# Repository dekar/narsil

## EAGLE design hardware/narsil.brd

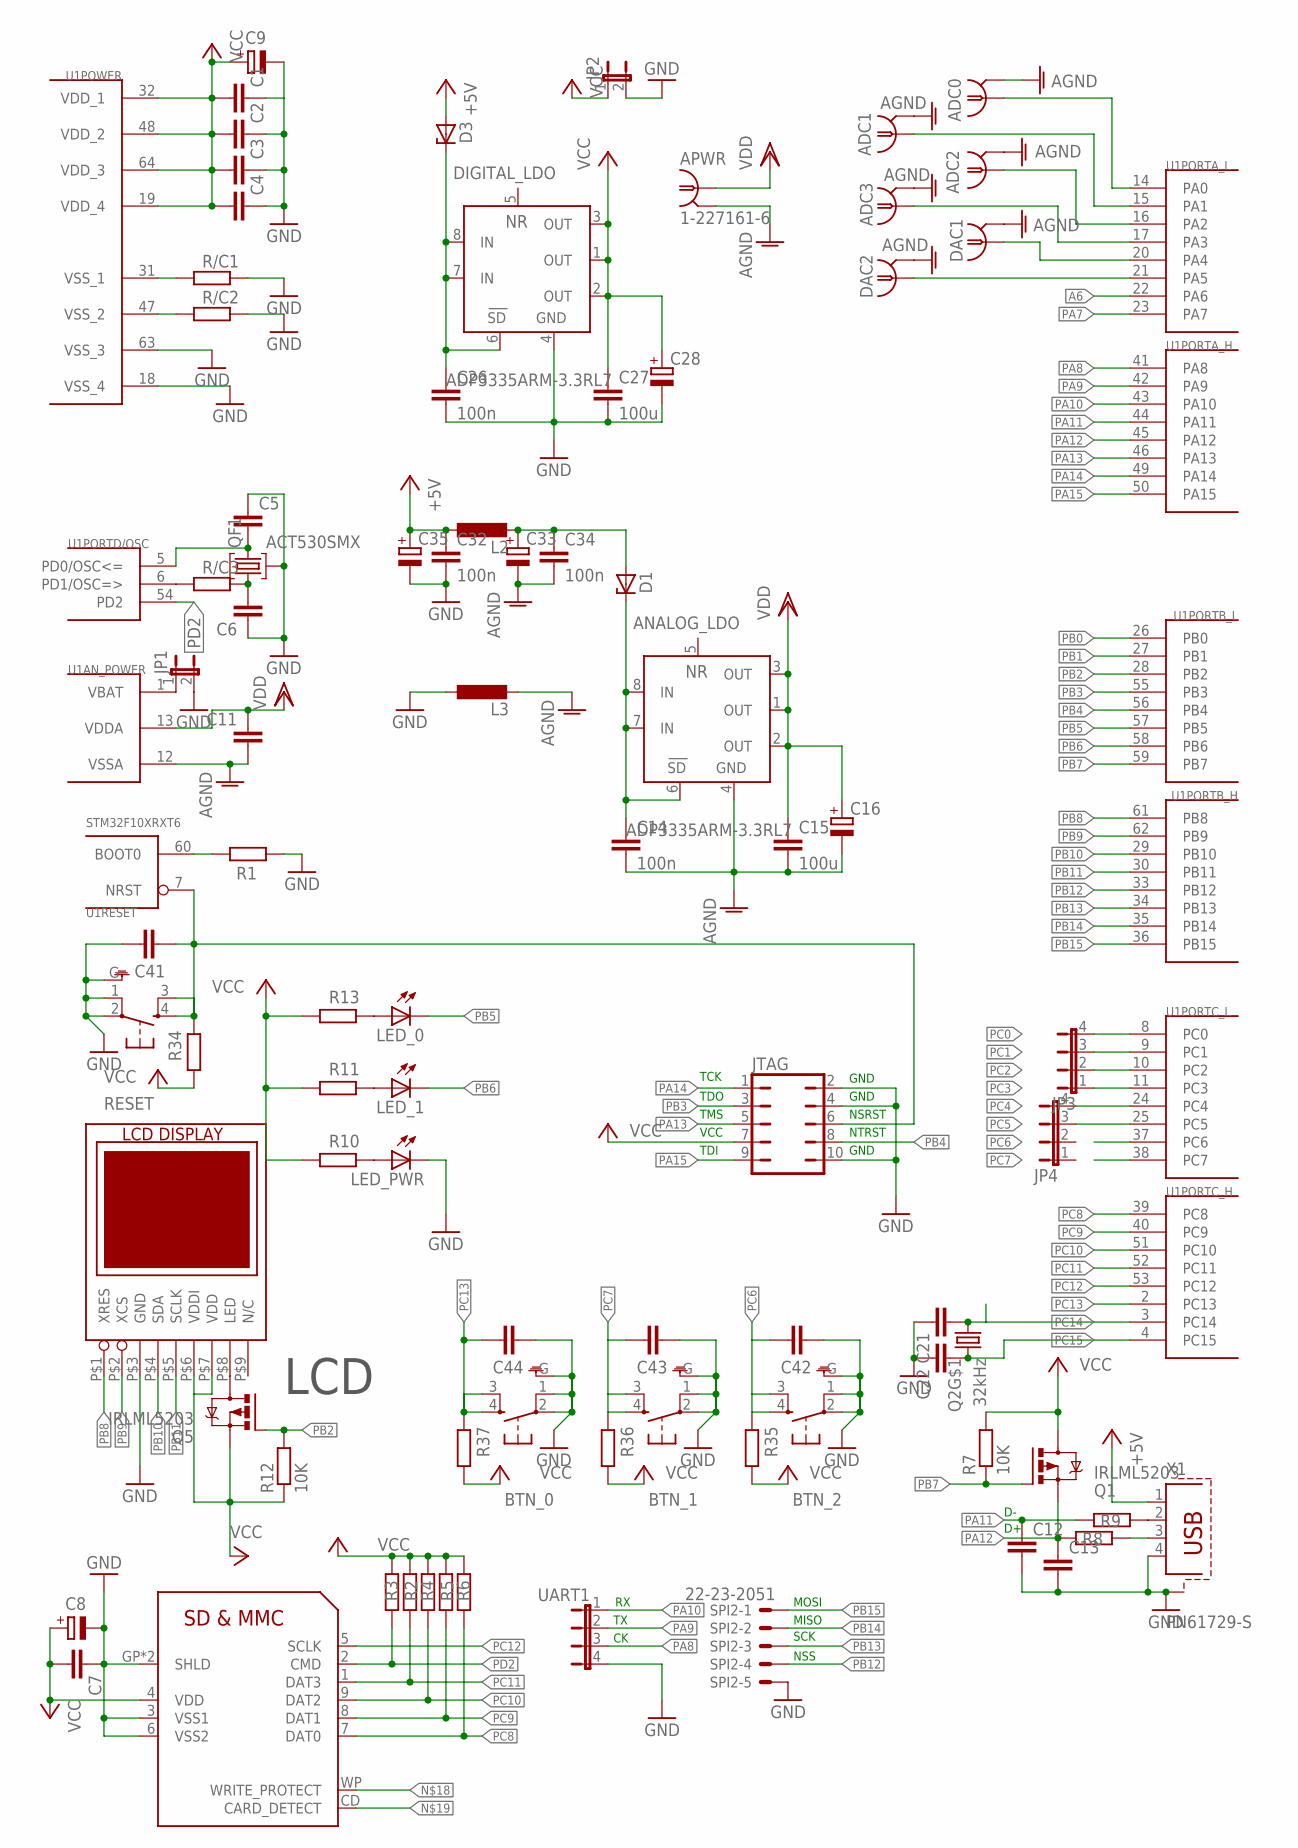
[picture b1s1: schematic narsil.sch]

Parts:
ADC0, ADC1, ADC2: 1-227161-6; AMP_227161
ADC3: 1-227161-6; AMP_227161; MPN 1-227161-6
ANALOG_LDO: ADP3335ARM-3.3RL7; MSOP08
APWR: 1-227161-6; AMP_227161
BTN_0, BTN_1, BTN_2: 10-XXG; B3F-10XXG
C1, C2, C3, C4, C5, C6, C7, C11, C12, C13, C21, C22, C41, C42, C43, C44: C-EUC0805; C0805
C8, C9, C16, C28, C33, C35: CPOL-EUSMCA; SMC_A
C14, C26, C32, C34: 100n; C0805
C15, C27: 100u; C0805
D1, D3: ZENER-DIODESMB; SMB
DAC1, DAC2: 1-227161-6; AMP_227161
DIGITAL_LDO: ADP3335ARM-3.3RL7; MSOP08
JP1, JP2: JP1E; JP1
JP3, JP4: JP4E; JP4
JTAG: JP5Q
L2, L3: L-EUL1206; R1206
LED_0, LED_1: LEDSMT1206; 1206
LED_PWR: LEDSMT1206; 1206
Q1, Q5: IRLML5203; MICRO3
Q2: 32kHz; MC146
QF1: ACT530SMX
R1, R10, R11, R13, R34, R35, R36, R37: 5k; M0805
R2, R3, R4, R5, R6, R8, R9: 47k; M0805
R7, R12: 10K; M0805
R/C1, R/C2, R/C3: R-EU_M0805; M0805
RESET: 10-XXG; B3F-10XXG
SPI2: 22-23-2051
U1: STM32F10XRXT6; TQFP64
U$1: SD-RSMT-2-MQ
U$2: LCD; LCD_NOKIA1100
UART1: JP4E; JP4
X1: PN61729-S

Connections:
+5V: C32.1, C35.+, D3.A, L2.1, X1.1
A6: U1.22 (PA6)
AGND: ADC0.2 (GND), ADC1.2 (GND), ADC2.2 (GND), ADC3.2 (GND), ANALOG_LDO.4 (GND), APWR.2 (GND), C11.2, C14.2, C15.2, C16.-, C33.-, C34.2, DAC1.2 (GND), DAC2.2 (GND), L3.2, U1.12 (VSSA)
GND: BTN_0.1, BTN_0.2, BTN_0.G (GND), BTN_1.1, BTN_1.2, BTN_1.G (GND), BTN_2.1, BTN_2.2, BTN_2.G (GND), C1.1, C2.1, C3.1, C4.1, C5.1, C6.1, C7.1, C8.-, C9.-, C12.2, C13.2, C21.1, C22.1, C26.2, C27.2, C28.-, C32.2, C35.-, C41.1, C42.1, C43.1, C44.1, DIGITAL_LDO.4 (GND), JP1.2, JP2.2, JTAG.2, JTAG.4, JTAG.10, L3.1, LED_PWR.C, Q2.GND, Q2.GND2 (GND), QF1.S$1 (2), QF1.S$2 (2), R1.1, R/C1.1, R/C2.1, RESET.1, RESET.2, RESET.G (GND), SPI2.5, U1.18 (VSS_4), U1.63 (VSS_3), U$1.3 (VSS1), U$1.6 (VSS2), U$1.GP (SHLD), U$1.GP2 (SHLD), U$2.P$3 (GND), UART1.4, X1.4, X1.SHLD@1 (S1), X1.SHLD@2 (S1)
unnamed: R/C2.2, U1.47 (VSS_2)
unnamed: R/C1.2, U1.31 (VSS_1)
unnamed: C5.2, QF1.P2 (3), U1.5 (PD0/OSC<=)
unnamed: C6.2, QF1.P1 (1), R/C3.1
unnamed: DAC1.1, U1.20 (PA4)
unnamed: DAC2.1, U1.21 (PA5)
unnamed: ADC3.1, U1.17 (PA3)
unnamed: ADC2.1, U1.16 (PA2)
unnamed: ADC1.1, U1.15 (PA1)
unnamed: ADC0.1, U1.14 (PA0)
unnamed: R1.2, U1.60 (BOOT0)
unnamed: Q5.3 (D), U$2.P$8 (LED)
unnamed: LED_PWR.A, R10.2
unnamed: R9.1, X1.2
unnamed: LED_1.A, R11.2
unnamed: R8.1, X1.3
unnamed: LED_0.A, R13.2
unnamed: JP1.1, U1.1 (VBAT)
unnamed: ANALOG_LDO.6 (SD/), ANALOG_LDO.7 (IN), ANALOG_LDO.8 (IN), C14.1, D1.C
unnamed: R/C3.2, U1.6 (PD1/OSC=>)
unnamed: C33.+, C34.1, D1.A, L2.2
unnamed: C41.2, JTAG.6, R34.2, RESET.3 (S1), RESET.4 (S), U1.7 (NRST)
unnamed: C26.1, D3.C, DIGITAL_LDO.6 (SD/), DIGITAL_LDO.7 (IN), DIGITAL_LDO.8 (IN)
PA7: U1.23 (PA7)
PA8: U1.41 (PA8), UART1.3
PA9: U1.42 (PA9), UART1.2
PA10: U1.43 (PA10), UART1.1
PA11: C12.1, R9.2, U1.44 (PA11)
PA12: C13.1, Q1.2 (S), R8.2, U1.45 (PA12)
PA13: JTAG.5, U1.46 (PA13)
PA14: JTAG.1, U1.49 (PA14)
PA15: JTAG.9, U1.50 (PA15)
PB0: U1.26 (PB0)
PB1: U1.27 (PB1)
PB2: Q5.1 (G), R12.2, U1.28 (PB2)
PB3: JTAG.3, U1.55 (PB3)
PB4: JTAG.8, U1.56 (PB4)
PB5: LED_0.C, U1.57 (PB5)
PB6: LED_1.C, U1.58 (PB6)
PB7: Q1.1 (G), R7.1, U1.59 (PB7)
PB8: U1.61 (PB8), U$2.P$1 (XRES)
PB9: U1.62 (PB9), U$2.P$2 (XCS)
PB10: U1.29 (PB10), U$2.P$4 (SDA)
PB11: U1.30 (PB11), U$2.P$5 (SCLK)
PB12: SPI2.4, U1.33 (PB12)
PB13: SPI2.3, U1.34 (PB13)
PB14: SPI2.2, U1.35 (PB14)
PB15: SPI2.1, U1.36 (PB15)
PC0: JP3.4, U1.8 (PC0)
PC1: JP3.3, U1.9 (PC1)
PC2: JP3.2, U1.10 (PC2)
PC3: JP3.1, U1.11 (PC3)
PC4: JP4.4, U1.24 (PC4)
PC5: JP4.3, U1.25 (PC5)
PC6: BTN_2.3 (S1), BTN_2.4 (S), C42.2, R35.2, U1.37 (PC6)
PC7: BTN_1.3 (S1), BTN_1.4 (S), C43.2, R36.2, U1.38 (PC7)
PC8: R6.1, U1.39 (PC8), U$1.7 (DAT0)
PC9: R5.1, U1.40 (PC9), U$1.8 (DAT1)
PC10: R4.1, U1.51 (PC10), U$1.9 (DAT2)
PC11: R2.1, U1.52 (PC11), U$1.1 (DAT3)
PC12: U1.53 (PC12), U$1.5 (SCLK)
PC13: BTN_0.3 (S1), BTN_0.4 (S), C44.2, R37.2, U1.2 (PC13)
PC14: C21.2, Q2.P$1 (1), U1.3 (PC14)
PC15: C22.2, Q2.P$2 (2), U1.4 (PC15)
PD2: R3.1, U1.54 (PD2), U$1.2 (CMD)
VCC: C1.2, C2.2, C3.2, C4.2, C7.2, C8.+, C9.+, C27.1, C28.+, DIGITAL_LDO.1 (OUT), DIGITAL_LDO.2 (OUT), DIGITAL_LDO.3 (OUT), JP2.1, JTAG.7, Q1.3 (D), Q5.2 (S), R2.2, R3.2, R4.2, R5.2, R6.2, R7.2, R10.1, R11.1, R12.1, R13.1, R34.1, R35.1, R36.1, R37.1, U1.19 (VDD_4), U1.32 (VDD_1), U1.48 (VDD_2), U1.64 (VDD_3), U$1.4 (VDD), U$2.P$6 (VDDI), U$2.P$7 (VDD)
VDD: ANALOG_LDO.1 (OUT), ANALOG_LDO.2 (OUT), ANALOG_LDO.3 (OUT), APWR.1, C11.1, C15.1, C16.+, U1.13 (VDDA)

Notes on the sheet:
LCD
MOSI
MISO
SCK
NSS
TCK
TDO
TMS
VCC
TDI
GND
NSRST
NTRST

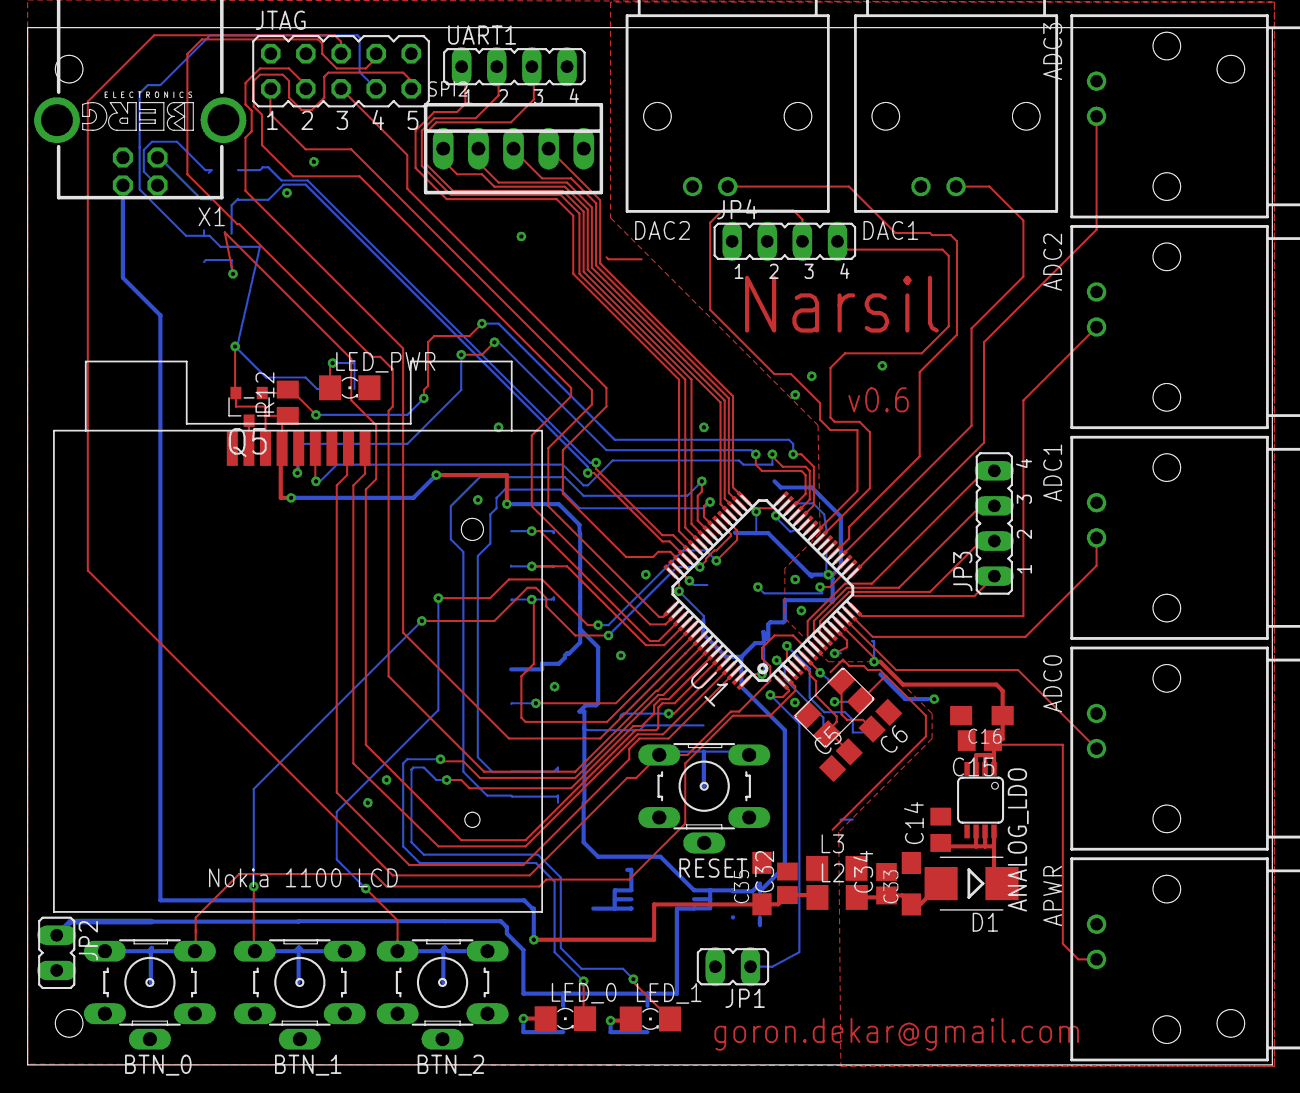
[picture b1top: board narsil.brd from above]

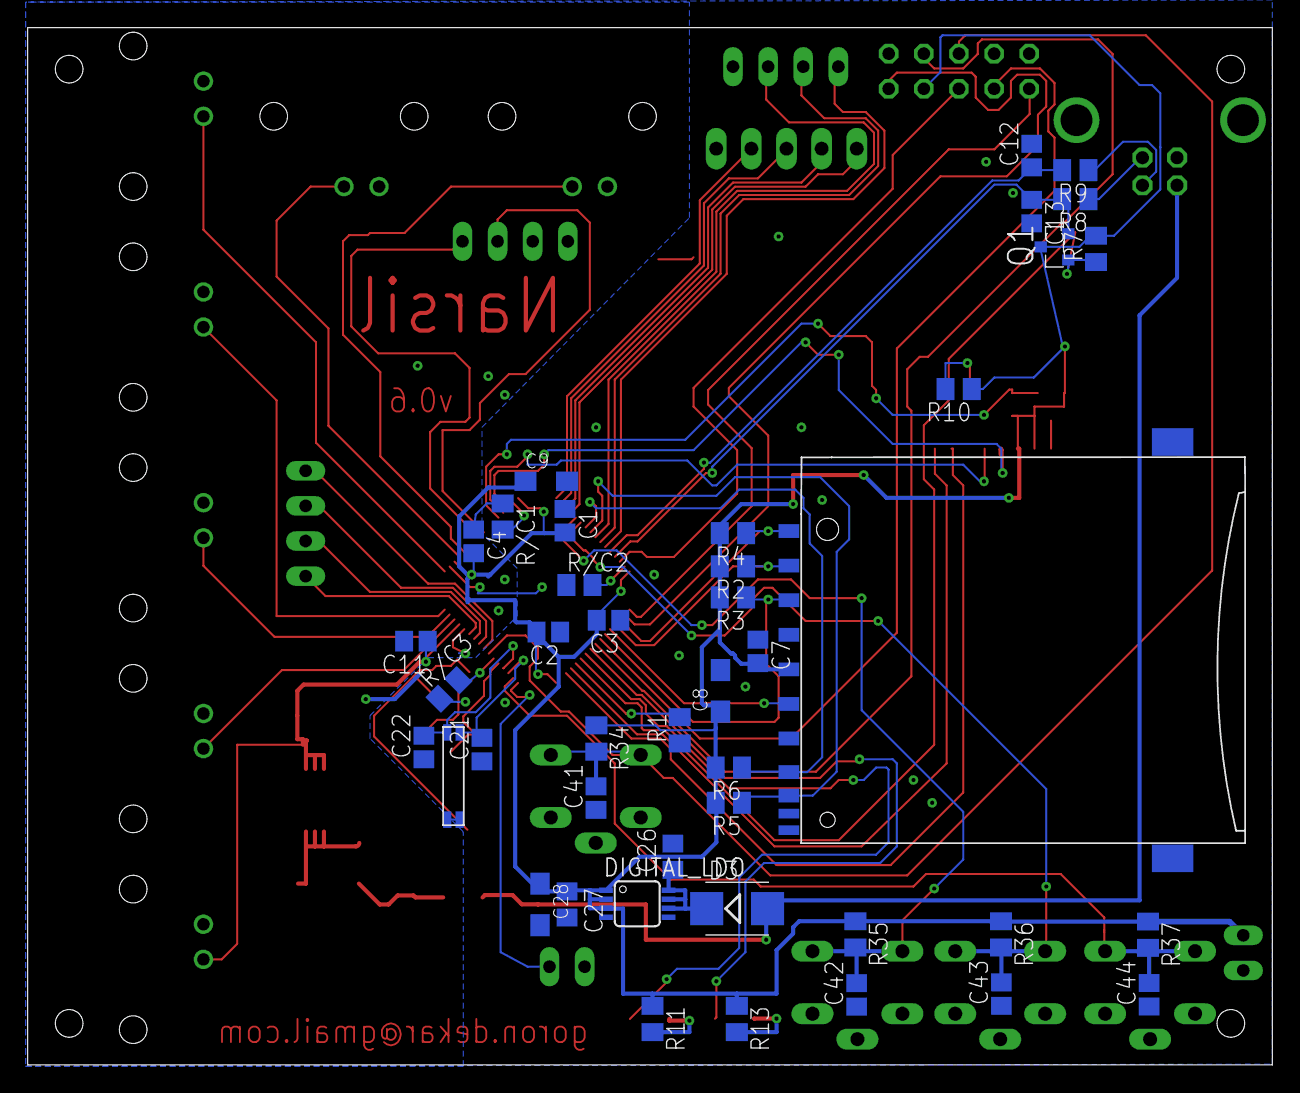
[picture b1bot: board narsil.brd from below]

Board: 2 copper layers, 90.0 x 75.0 mm, 83 parts (43 on the bottom side), 67 nets.

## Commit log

2012-02-23 Narsil begined
2012-02-24 Schematic ready
2012-02-24 layout is close to ready: there is no LCD only
2012-02-24 v0.4 OK
2012-02-24 v0.5
2012-02-24 v0.6
2015-04-16 Migrating wiki contents from Google Code
2015-04-16 Add license
2015-04-16 add software and license
